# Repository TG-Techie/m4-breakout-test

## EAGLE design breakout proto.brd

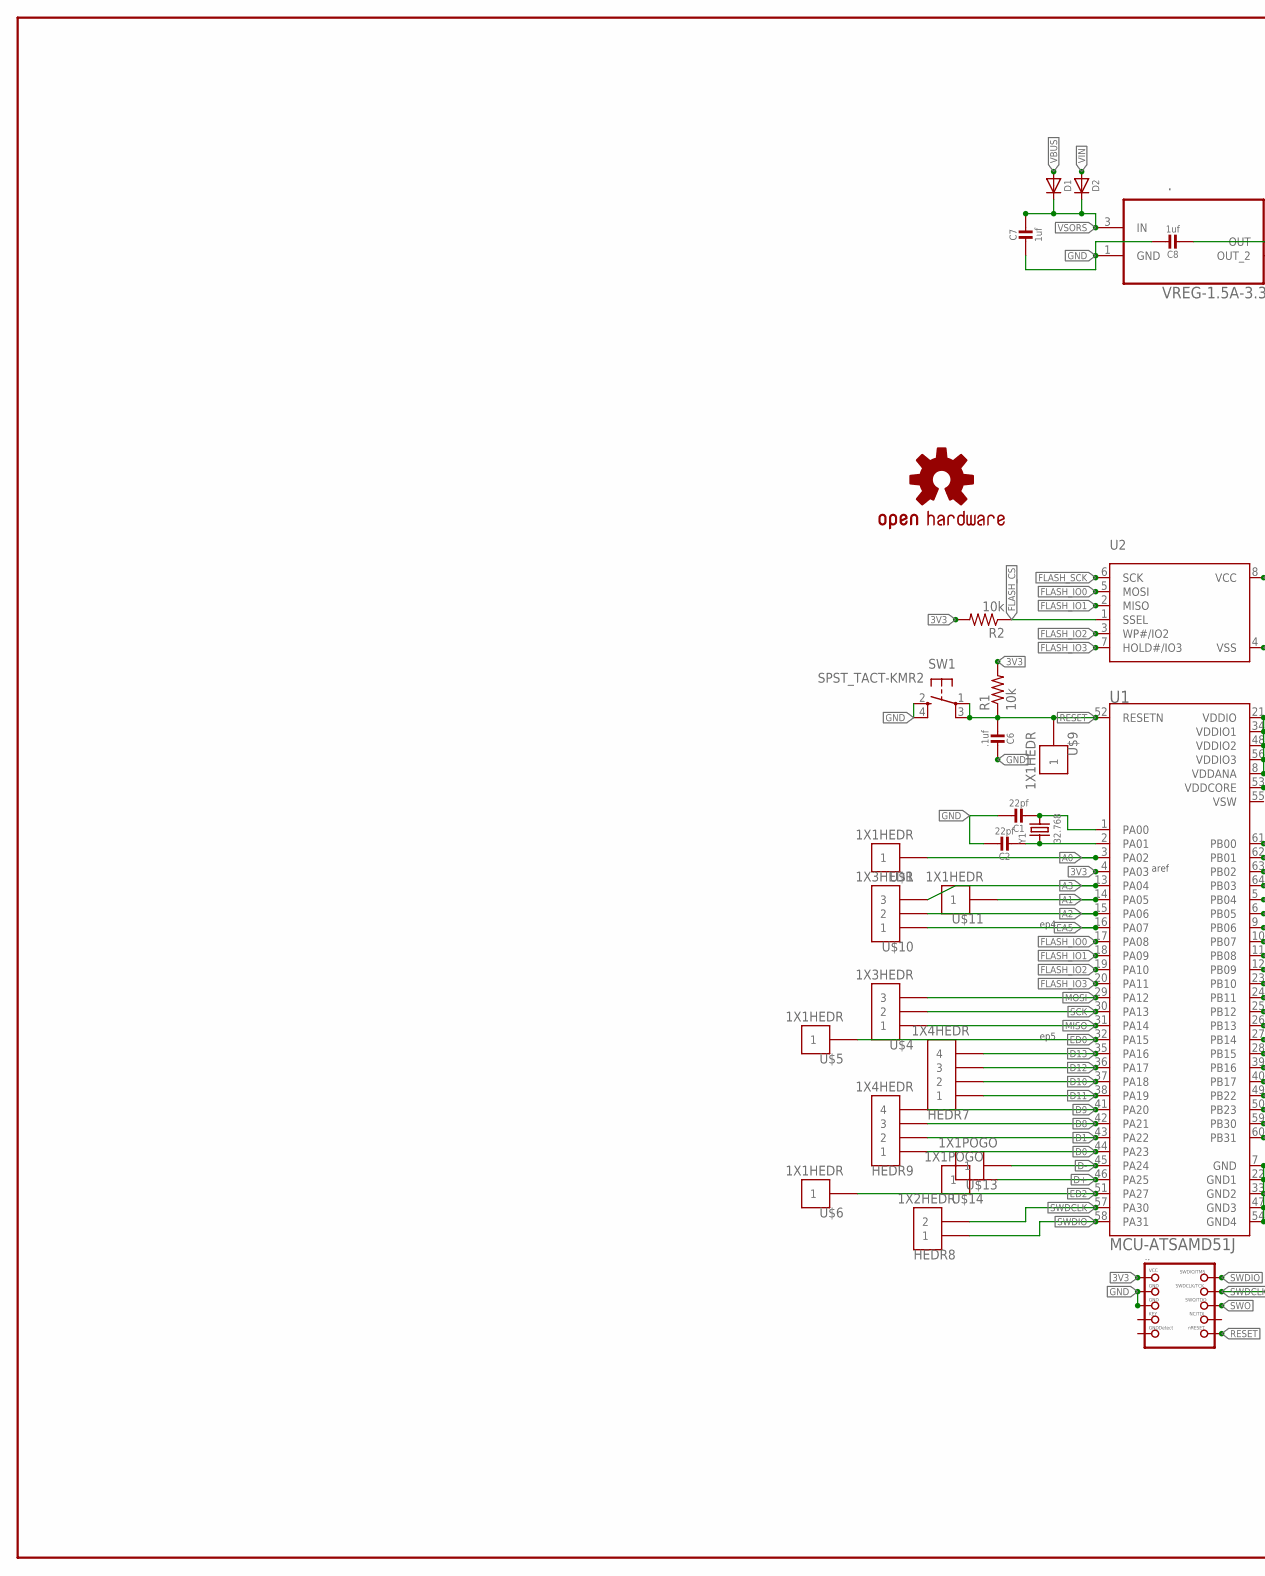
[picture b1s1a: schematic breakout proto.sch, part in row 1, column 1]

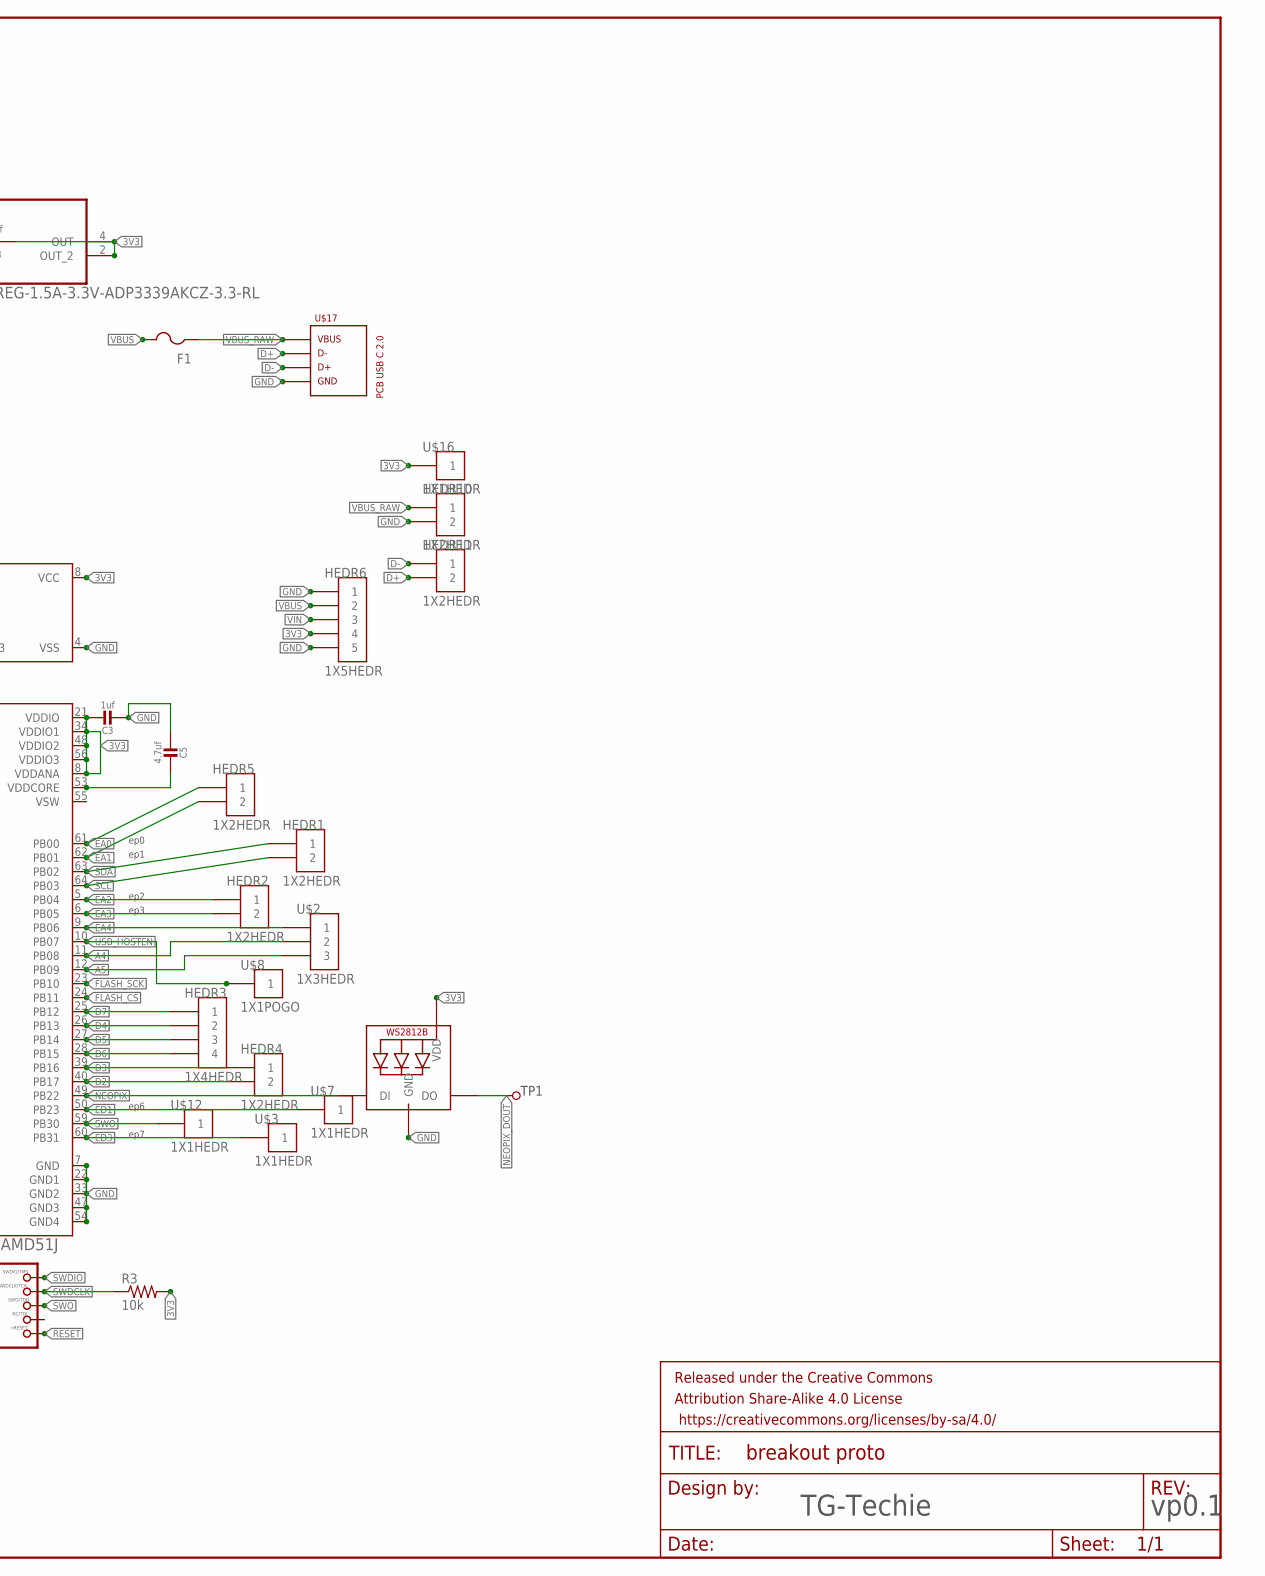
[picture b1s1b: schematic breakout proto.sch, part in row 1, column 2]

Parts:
.: VREG-1.5A-3.3V-ADP3339AKCZ-3.3-RL; SOT230P700X180-4N
..: INTRFC-JTAG-CORTEXBOXPOSTS; 2X05_1.27MM_BOX_POSTS
C1, C2: 22pf; MICROBUILDER__0805
C3, C7, C8: 1uf; MICROBUILDER__0805
C5: 4.7uf; MICROBUILDER__0805
C6: .1uf; MICROBUILDER__0805
D1, D2: DIODESOD-123; SOD-123
F1: PTCFUSE-1206; R1206
FRAME1: FRAME-LEDGER; CREATIVE_COMMONS
HEDR1, HEDR2, HEDR4, HEDR5, HEDR8, HEDR10, HEDR11: 1X2HEDR; 1X2_HEDR
HEDR3, HEDR7, HEDR9: 1X4HEDR; 1X4_HEDR
HEDR6: 1X5HEDR; 1X5_HEDR
LED1: LED-NEO-WS2812B3535; LED3535
LOGO1: OSHW-LOGOMINI; OSHW-LOGO-MINI
R1, R2, R3: 10k; R0805
SW1: SPST_TACT-KMR2; KMR2
TP1: TESTPOINT_1X1; 1X1_POGO
U1: MCU-ATSAMD51J; QFP50P1200X1200X120-64N
U2: FLASH-SPI-SOIC8208MIL; SOIC8_208MIL
U$1, U$3, U$5, U$6, U$7, U$9, U$11, U$12, U$16: 1X1HEDR; 1X1_HEDR
U$2, U$4, U$10: 1X3HEDR; 1X3_HEDR
U$8, U$13, U$14: 1X1POGO; 1X1_POGO
U$17: USB-C-PCB-USB-2.0-TYPE-CDS_3; USB_TYPE_C_DS_3
Y1: 32.768; MICROBUILDER_CRYSTAL_4.9X1.8

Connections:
3V3: ..2 (OUT_2), ..4 (OUT), ...1 (VCC), C3.1, C8.2, HEDR6.4, LED1.2 (VDD), R1.2, R2.2, R3.2, U1.4 (PA03), U1.8 (VDDANA), U1.21 (VDDIO), U1.34 (VDDIO1), U1.48 (VDDIO2), U1.56 (VDDIO3), U2.8 (VCC), U$16.1
A0: U1.3 (PA02), U$1.1
A1: U1.14 (PA05), U$11.1
A2: U1.15 (PA06), U$10.2
A3: U1.13 (PA04), U$10.3
A4: U1.11 (PB08), U$2.2
A5: U1.12 (PB09), U$2.3
D0: HEDR9.1, U1.44 (PA23)
D1: HEDR9.2, U1.43 (PA22)
D2: HEDR4.2, U1.40 (PB17)
D3: HEDR4.1, U1.39 (PB16)
D4: HEDR3.2, U1.26 (PB13)
D5: HEDR3.3, U1.27 (PB14)
D6: HEDR3.4, U1.28 (PB15)
D7: HEDR3.1, U1.25 (PB12)
D8: HEDR9.3, U1.42 (PA21)
D9: HEDR9.4, U1.41 (PA20)
D10: HEDR7.2, U1.37 (PA18)
D11: HEDR7.1, U1.38 (PA19)
D12: HEDR7.3, U1.36 (PA17)
D13: HEDR7.4, U1.35 (PA16)
D+: HEDR11.2, U1.46 (PA25), U$14.1, U$17.A7 (D-), U$17.B7 (D-)
D-: HEDR11.1, U1.45 (PA24), U$13.1, U$17.A6 (D+), U$17.B6 (D+)
EA0: HEDR5.1, U1.61 (PB00)
EA1: HEDR5.2, U1.62 (PB01)
EA2: HEDR2.1, U1.5 (PB04)
EA3: HEDR2.2, U1.6 (PB05)
EA4: U1.9 (PB06), U$2.1
EA5: U1.16 (PA07), U$10.1
ED0: U1.32 (PA15), U$5.1
ED1: U1.50 (PB23), U$7.1
ED2: U1.51 (PA27), U$6.1
ED3: U1.60 (PB31), U$3.1
FLASH_CS: R2.1, U1.24 (PB11), U2.1 (SSEL)
FLASH_IO0: U1.17 (PA08), U2.5 (MOSI)
FLASH_IO1: U1.18 (PA09), U2.2 (MISO)
FLASH_IO2: U1.19 (PA10), U2.3 (WP#/IO2)
FLASH_IO3: U1.20 (PA11), U2.7 (HOLD#/IO3)
FLASH_SCK: U1.23 (PB10), U2.6 (SCK)
GND: ..1 (GND), ...3 (GND), ...5 (GND), C1.1, C2.2, C3.2, C5.2, C6.1, C7.2, C8.1, HEDR6.1, HEDR6.5, HEDR10.2, LED1.4 (GND), SW1.2 (S), SW1.4 (S1), U1.7 (GND), U1.22 (GND1), U1.33 (GND2), U1.47 (GND3), U1.54 (GND4), U2.4 (VSS), U$17.A1 (GND), U$17.A12 (GND), U$17.B1 (GND), U$17.B12 (GND)
MISO: U1.31 (PA14), U$4.1
MOSI: U1.29 (PA12), U$4.3
unnamed: C5.1, U1.53 (VDDCORE)
unnamed: C1.2, U1.1 (PA00), Y1.2
unnamed: C2.1, U1.2 (PA01), Y1.1
NEOPIX: LED1.1 (DI), U1.49 (PB22)
NEOPIX_DOUT: LED1.3 (DO), TP1.1
RESET: ...10 (NRESET), C6.2, R1.1, SW1.1, SW1.3 (P1), U1.52 (RESETN), U$9.1
SCK: U1.30 (PA13), U$4.2
SCL: HEDR1.2, U1.64 (PB03)
SDA: HEDR1.1, U1.63 (PB02)
SWDCLK: ...4 (SWDCLK), HEDR8.2, R3.1, U1.57 (PA30)
SWDIO: ...2 (SWDIO), HEDR8.1, U1.58 (PA31)
SWO: ...6 (SWO), U1.59 (PB30), U$12.1
USB_HOSTEN: U1.10 (PB07), U$8.1
VBUS: D1.A, F1.2, HEDR6.2
VBUS_RAW: F1.1, HEDR10.1, U$17.A4 (VBUS), U$17.A9 (VBUS), U$17.B4 (VBUS), U$17.B9 (VBUS)
VIN: D2.A, HEDR6.3
VSORS: ..3 (IN), C7.1, D1.C, D2.C
VSW: U1.55 (VSW)

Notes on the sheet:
aref
ep0
ep1
ep2
ep3
ep4
ep5
ep6
ep7
vp0.1
TG-Techie

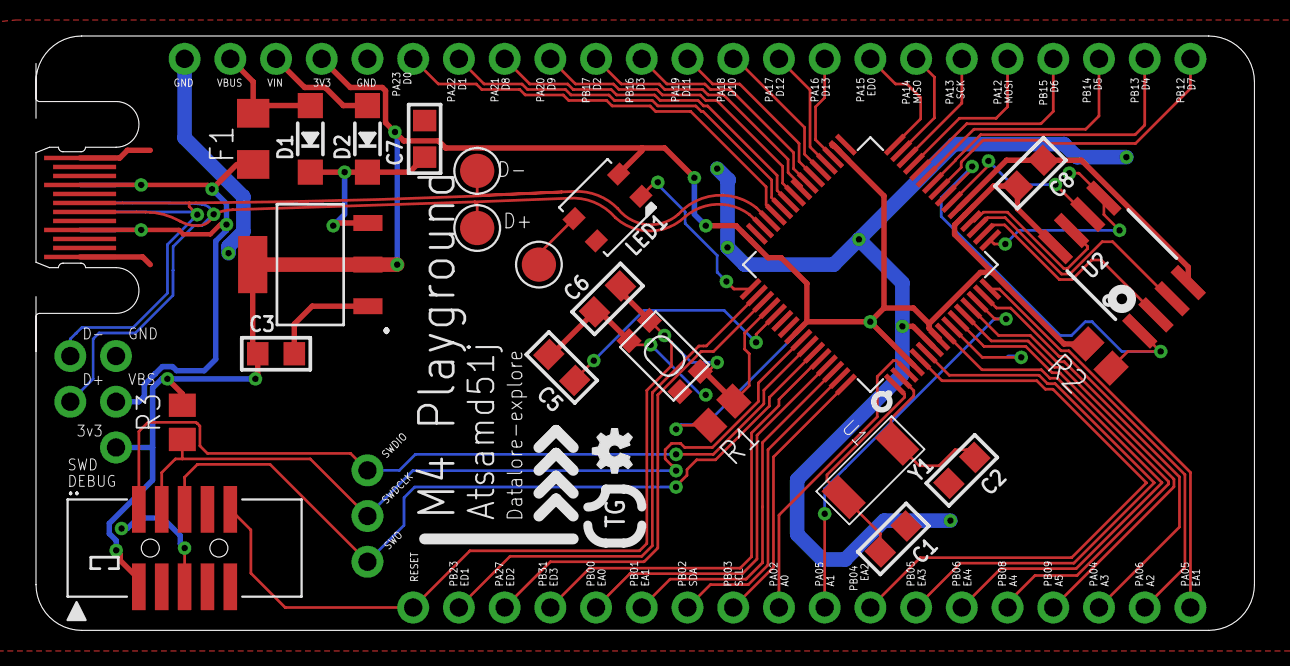
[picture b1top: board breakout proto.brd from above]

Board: 2 copper layers, 67.7 x 33.0 mm, 51 parts (1 on the bottom side), 59 nets.

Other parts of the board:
U$15: LOGO_TG_TEST_LARGE

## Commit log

2018-05-30 Add files via upload
    this is the first upload. as of now untested but reviewed multiple times. hi all!
    released under: https://creativecommons.org/licenses/by-nc/3.0/us/

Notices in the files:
parts and their libraries:
SparkFun-Aesthetics: Licensing: Creative Commons ShareAlike 4.0 International - https://creativecommons.org/licenses/by-sa/4.0
SparkFun-Aesthetics: Released under the Creative Commons Attribution Share-Alike 4.0 License
SparkFun-Aesthetics: https://creativecommons.org/licenses/by-sa/4.0
